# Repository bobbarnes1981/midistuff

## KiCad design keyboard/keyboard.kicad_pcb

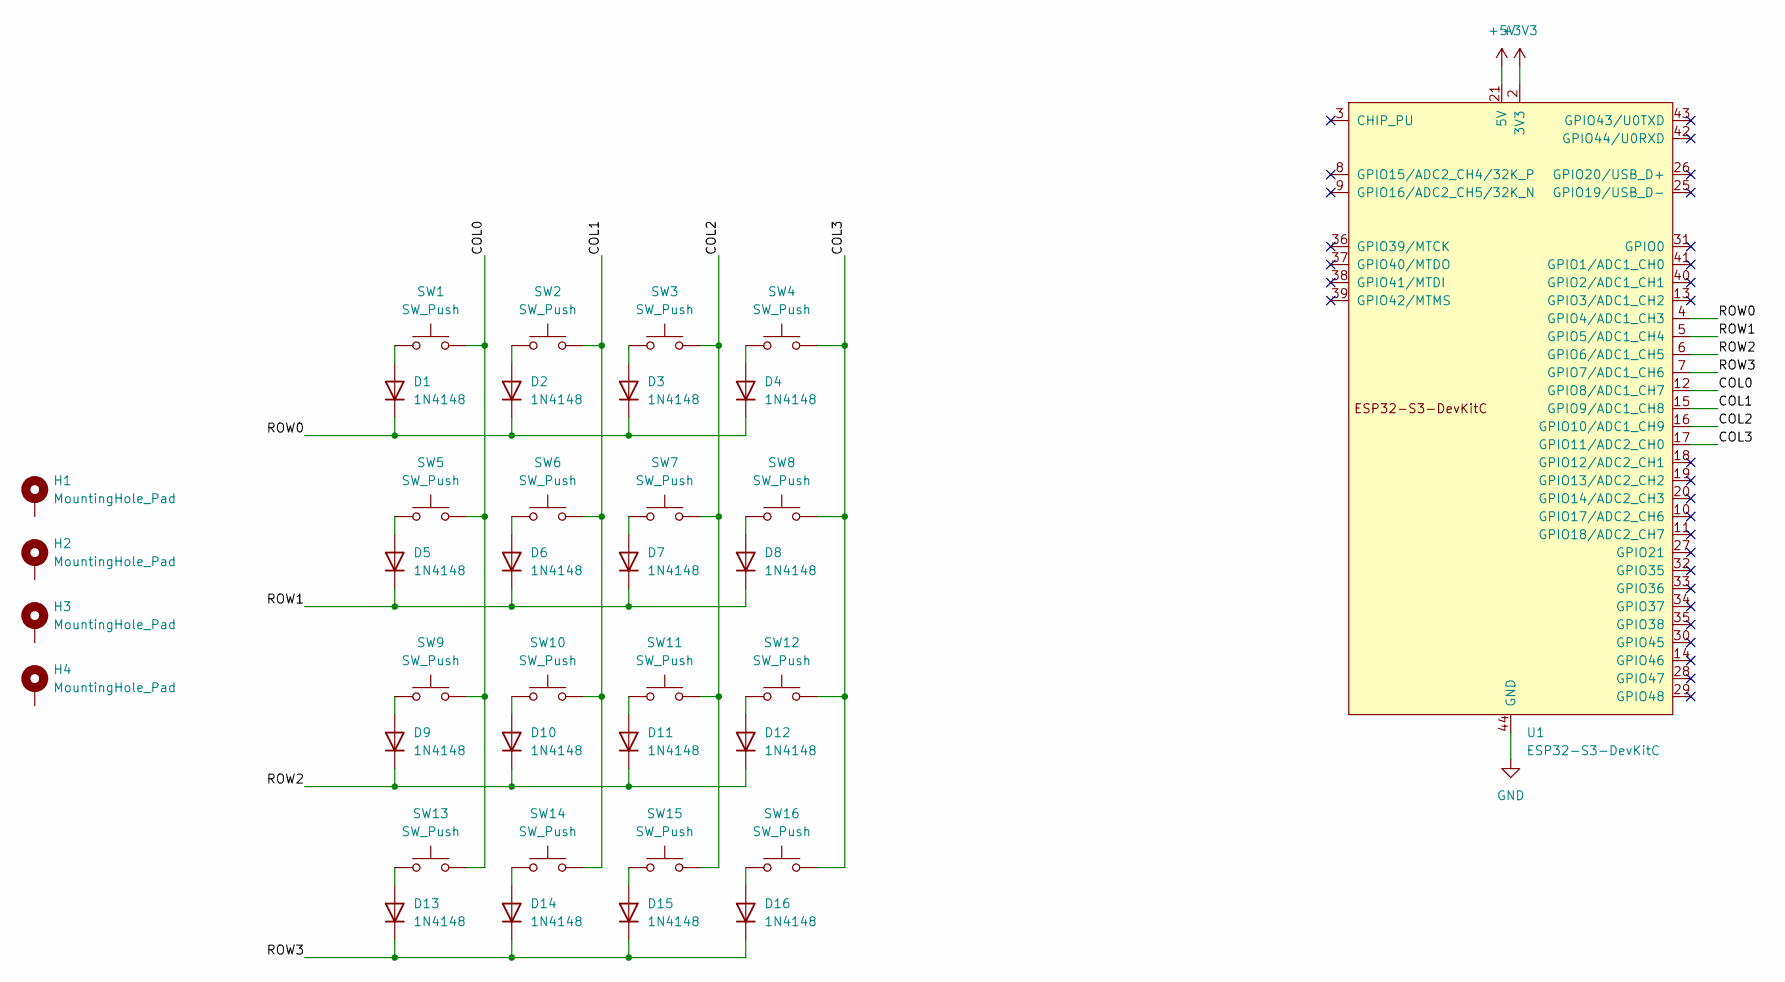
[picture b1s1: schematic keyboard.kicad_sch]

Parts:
D1, D2, D3, D4, D5, D6, D7, D8, D9, D10, D11, D12, D13, D14, D15, D16: 1N4148; D_DO-35_SOD27_P7.62mm_Horizontal
H1, H2, H3, H4: MountingHole_Pad; MountingHole_3.2mm_M3_Pad
SW1, SW2, SW3, SW4, SW5, SW6, SW7, SW8, SW9, SW10, SW11, SW12, SW13, SW14, SW15, SW16: SW_Push; SW_Hotswap_Kailh_MX_1.00u
U1: ESP32-S3-DevKitC

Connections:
+3V3: U1.1 (3V3), U1.2 (3V3)
+5V: U1.21 (5V)
/COL0: SW1.2, SW5.2, SW9.2, SW13.2, U1.12 (GPIO8/ADC1_CH7)
/COL1: SW2.2, SW6.2, SW10.2, SW14.2, U1.15 (GPIO9/ADC1_CH8)
/COL2: SW3.2, SW7.2, SW11.2, SW15.2, U1.16 (GPIO10/ADC1_CH9)
/COL3: SW4.2, SW8.2, SW12.2, SW16.2, U1.17 (GPIO11/ADC2_CH0)
/ROW0: D1.1 (K), D2.1 (K), D3.1 (K), D4.1 (K), U1.4 (GPIO4/ADC1_CH3)
/ROW1: D5.1 (K), D6.1 (K), D7.1 (K), D8.1 (K), U1.5 (GPIO5/ADC1_CH4)
/ROW2: D9.1 (K), D10.1 (K), D11.1 (K), D12.1 (K), U1.6 (GPIO6/ADC1_CH5)
/ROW3: D13.1 (K), D14.1 (K), D15.1 (K), D16.1 (K), U1.7 (GPIO7/ADC1_CH6)
GND: U1.22 (GND), U1.23 (GND), U1.24 (GND), U1.44 (GND)
unnamed: D1.2 (A), SW1.1
unnamed: D2.2 (A), SW2.1
unnamed: D3.2 (A), SW3.1
unnamed: D4.2 (A), SW4.1
unnamed: D5.2 (A), SW5.1
unnamed: D6.2 (A), SW6.1
unnamed: D7.2 (A), SW7.1
unnamed: D8.2 (A), SW8.1
unnamed: D9.2 (A), SW9.1
unnamed: D10.2 (A), SW10.1
unnamed: D11.2 (A), SW11.1
unnamed: D12.2 (A), SW12.1
unnamed: D13.2 (A), SW13.1
unnamed: D14.2 (A), SW14.1
unnamed: D15.2 (A), SW15.1
unnamed: D16.2 (A), SW16.1

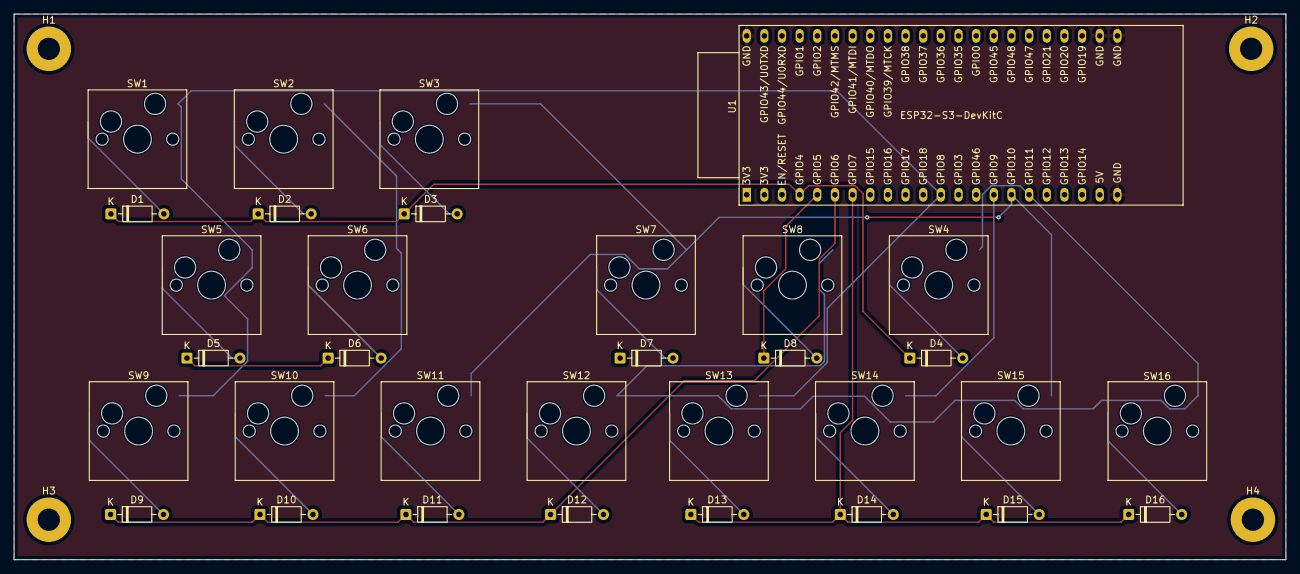
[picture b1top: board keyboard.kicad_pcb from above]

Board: 2 copper layers, 183.0 x 78.5 mm, 37 parts (0 on the bottom side), 26 nets.
